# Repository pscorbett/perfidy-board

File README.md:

# perfidy-board
A truely diabolitcal perf board.

## Project Description
Generic perf board with a surprise mid-layer routing. I wouldn't wish this on my worst enemies!

## Manufacturing Note
If, for some godforesaken reason, you decide to produce this idiotic perf board, there are a few things you should be aware of:
1) I have never produced or tested it (Why would I??)
2) You need to select 4-layer manufacturing, which will be slightly more expensive than simple 2-layer boards. The board is set up with JLC PCB rules (but again, untested)
3) You will lose all of your friends

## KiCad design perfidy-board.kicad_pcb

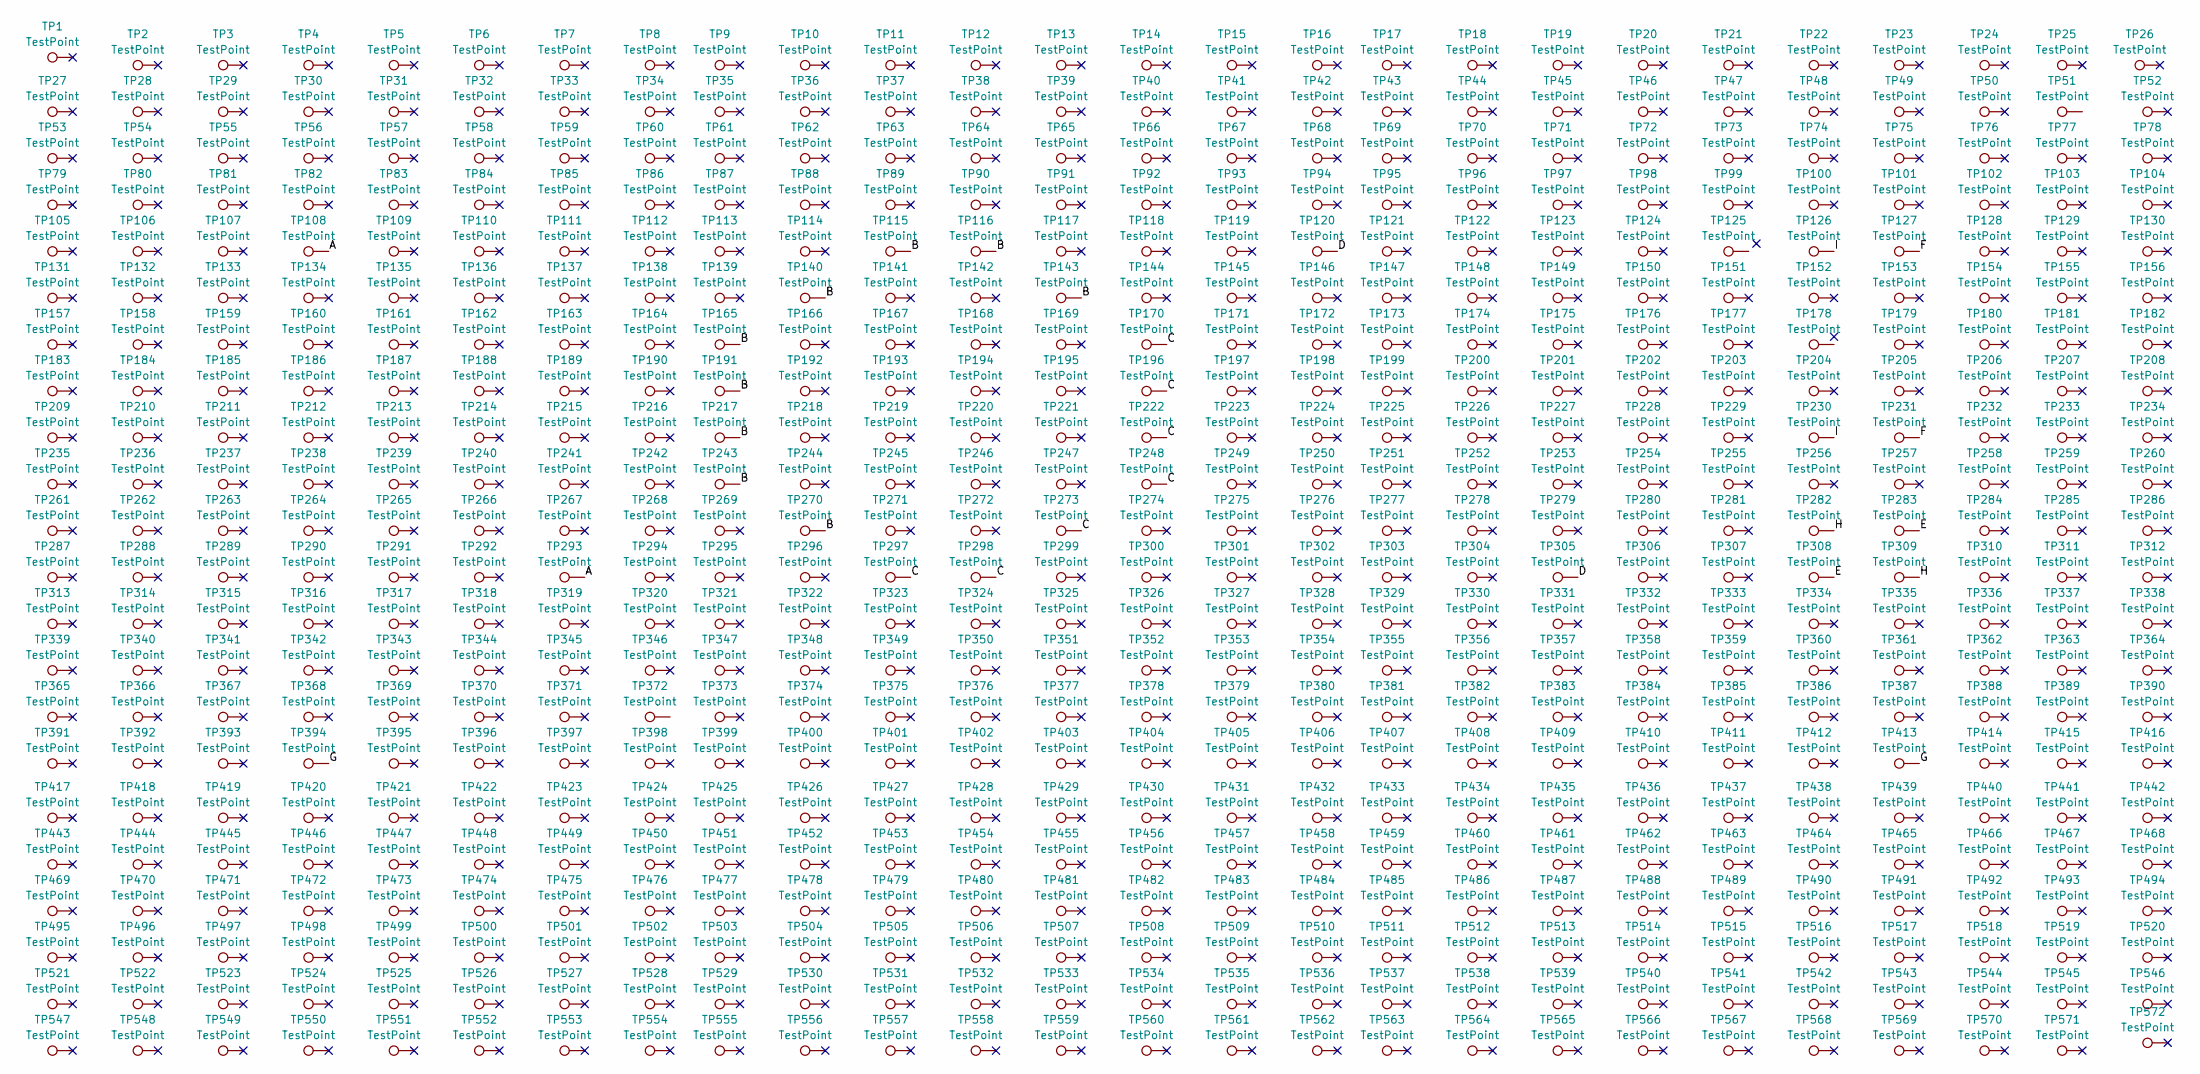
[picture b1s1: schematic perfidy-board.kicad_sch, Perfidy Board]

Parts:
TP1, TP26, TP547, TP572: TestPoint; Modified_MountingHole_3.2mm_M3_DIN965_Pad
TP2, TP3, TP4, TP5, TP6, TP7, TP8, TP9, TP10, TP11, TP12, TP13, TP14, TP15, TP16, TP17, TP18, TP19, TP20, TP21, TP22, TP23, TP24, TP25, TP27, TP28, TP29, TP30, TP31, TP32, TP33, TP34, TP35, TP36, TP37, TP38, TP39, TP40, TP41, TP42, TP43, TP44, TP45, TP46, TP47, TP48, TP49, TP50, TP51, TP52, TP53, TP54, TP55, TP56, TP57, TP58, TP59, TP60, TP61, TP62, TP63, TP64, TP65, TP66, TP67, TP68, TP69, TP70, TP71, TP72, TP73, TP74, TP75, TP76, TP77, TP78, TP79, TP80, TP81, TP82, TP83, TP84, TP85, TP86, TP87, TP88, TP89, TP90, TP91, TP92, TP93, TP94, TP95, TP96, TP97, TP98, TP99, TP100, TP101, TP102, TP103, TP104, TP105, TP106, TP107, TP108, TP109, TP110, TP111, TP112, TP113, TP114, TP115, TP116, TP117, TP118, TP119, TP120, TP121, TP122, TP123, TP124, TP125, TP126, TP127, TP128, TP129, TP130, TP131, TP132, TP133, TP134, TP135, TP136, TP137, TP138, TP139, TP140, TP141, TP142, TP143, TP144, TP145, TP146, TP147, TP148, TP149, TP150, TP151, TP152, TP153, TP154, TP155, TP156, TP157, TP158, TP159, TP160, TP161, TP162, TP163, TP164, TP165, TP166, TP167, TP168, TP169, TP170, TP171, TP172, TP173, TP174, TP175, TP176, TP177, TP178, TP179, TP180, TP181, TP182, TP183, TP184, TP185, TP186, TP187, TP188, TP189, TP190, TP191, TP192, TP193, TP194, TP195, TP196, TP197, TP198, TP199, TP200, TP201, TP202, TP203, TP204, TP205, TP206, TP207, TP208, TP209, TP210, TP211, TP212, TP213, TP214, TP215, TP216, TP217, TP218, TP219, TP220, TP221, TP222, TP223, TP224, TP225, TP226, TP227, TP228, TP229, TP230, TP231, TP232, TP233, TP234, TP235, TP236, TP237, TP238, TP239, TP240, TP241, TP242, TP243, TP244, TP245, TP246, TP247, TP248, TP249, TP250, TP251, TP252, TP253, TP254, TP255, TP256, TP257, TP258, TP259, TP260, TP261, TP262, TP263, TP264, TP265, TP266, TP267, TP268, TP269, TP270, TP271, TP272, TP273, TP274, TP275, TP276, TP277, TP278, TP279, TP280, TP281, TP282, TP283, TP284, TP285, TP286, TP287, TP288, TP289, TP290, TP291, TP292, TP293, TP294, TP295, TP296, TP297, TP298, TP299, TP300, TP301, TP302, TP303, TP304, TP305, TP306, TP307, TP308, TP309, TP310, TP311, TP312, TP313, TP314, TP315, TP316, TP317, TP318, TP319, TP320, TP321, TP322, TP323, TP324, TP325, TP326, TP327, TP328, TP329, TP330, TP331, TP332, TP333, TP334, TP335, TP336, TP337, TP338, TP339, TP340, TP341, TP342, TP343, TP344, TP345, TP346, TP347, TP348, TP349, TP350, TP351, TP352, TP353, TP354, TP355, TP356, TP357, TP358, TP359, TP360, TP361, TP362, TP363, TP364, TP365, TP366, TP367, TP368, TP369, TP370, TP371, TP372, TP373, TP374, TP375, TP376, TP377, TP378, TP379, TP380, TP381, TP382, TP383, TP384, TP385, TP386, TP387, TP388, TP389, TP390, TP391, TP392, TP393, TP394, TP395, TP396, TP397, TP398, TP399, TP400, TP401, TP402, TP403, TP404, TP405, TP406, TP407, TP408, TP409, TP410, TP411, TP412, TP413, TP414, TP415, TP416, TP417, TP418, TP419, TP420, TP421, TP422, TP423, TP424, TP425, TP426, TP427, TP428, TP429, TP430, TP431, TP432, TP433, TP434, TP435, TP436, TP437, TP438, TP439, TP440, TP441, TP442, TP443, TP444, TP445, TP446, TP447, TP448, TP449, TP450, TP451, TP452, TP453, TP454, TP455, TP456, TP457, TP458, TP459, TP460, TP461, TP462, TP463, TP464, TP465, TP466, TP467, TP468, TP469, TP470, TP471, TP472, TP473, TP474, TP475, TP476, TP477, TP478, TP479, TP480, TP481, TP482, TP483, TP484, TP485, TP486, TP487, TP488, TP489, TP490, TP491, TP492, TP493, TP494, TP495, TP496, TP497, TP498, TP499, TP500, TP501, TP502, TP503, TP504, TP505, TP506, TP507, TP508, TP509, TP510, TP511, TP512, TP513, TP514, TP515, TP516, TP517, TP518, TP519, TP520, TP521, TP522, TP523, TP524, TP525, TP526, TP527, TP528, TP529, TP530, TP531, TP532, TP533, TP534, TP535, TP536, TP537, TP538, TP539, TP540, TP541, TP542, TP543, TP544, TP545, TP546, TP548, TP549, TP550, TP551, TP552, TP553, TP554, TP555, TP556, TP557, TP558, TP559, TP560, TP561, TP562, TP563, TP564, TP565, TP566, TP567, TP568, TP569, TP570, TP571: TestPoint; Modified_TestPoint_THTPad_2.0x2.0mm_Drill1.0mm

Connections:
/A: TP108.1, TP293.1
/B: TP115.1, TP116.1, TP140.1, TP143.1, TP165.1, TP191.1, TP217.1, TP243.1, TP270.1
/C: TP170.1, TP196.1, TP222.1, TP248.1, TP273.1, TP297.1, TP298.1
/D: TP120.1, TP305.1
/E: TP283.1, TP308.1
/F: TP127.1, TP231.1
/G: TP394.1, TP413.1
/H: TP282.1, TP309.1
/I: TP126.1, TP230.1

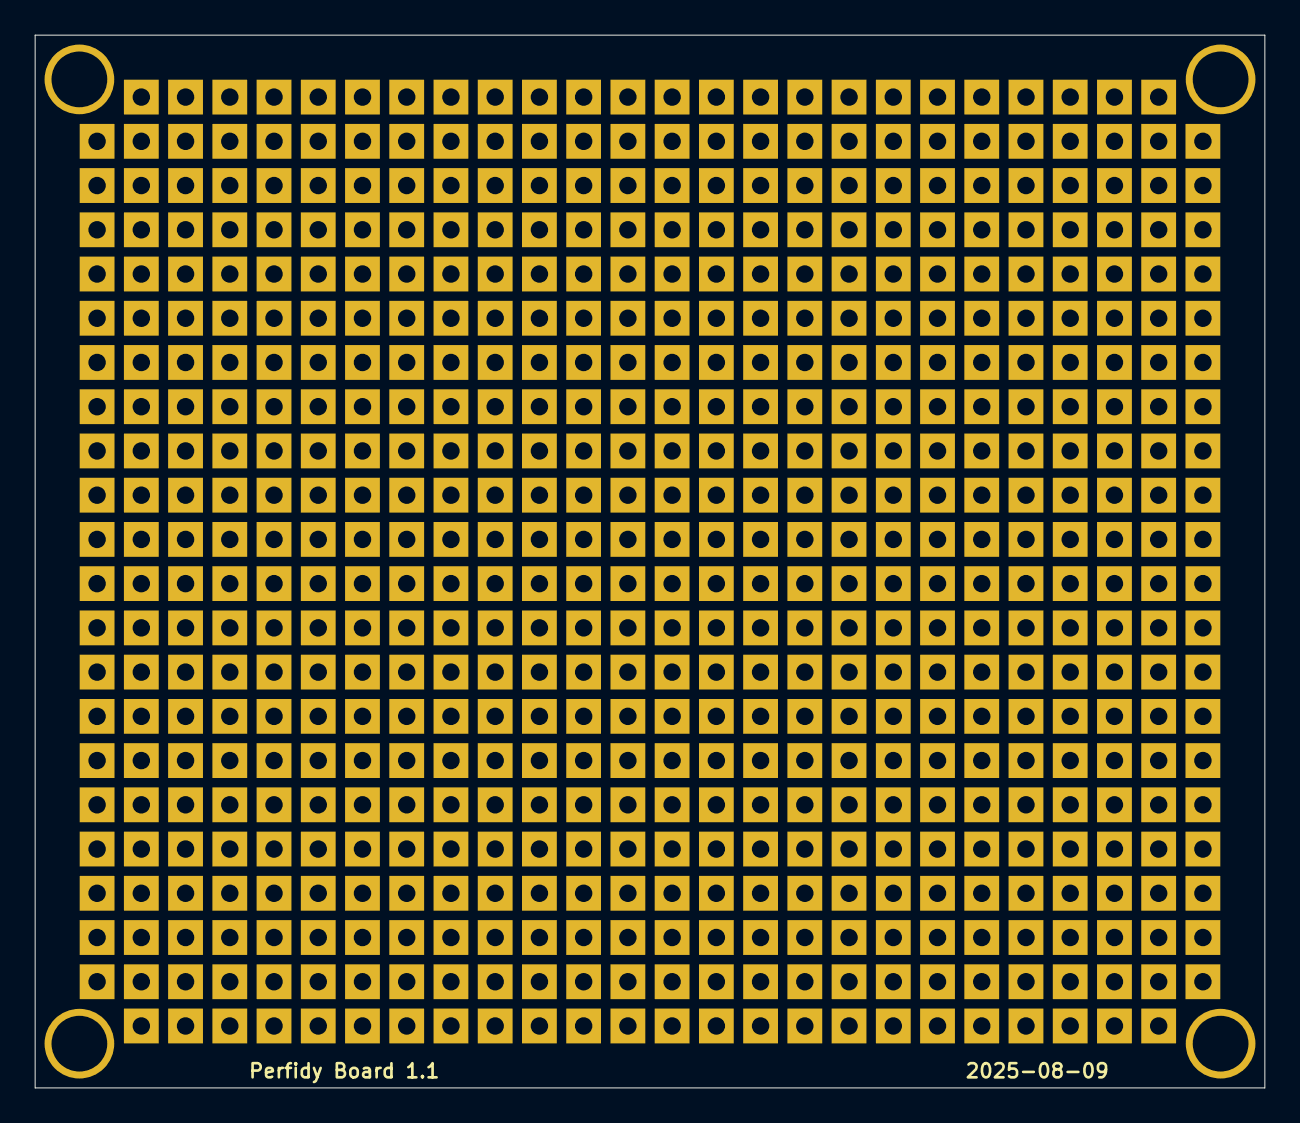
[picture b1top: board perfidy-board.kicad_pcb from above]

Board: 4 copper layers, 70.6 x 60.5 mm, 572 parts (0 on the bottom side), 9 nets.

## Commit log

2025-08-09 updating readme
    updating readme
2025-08-09 project update
2025-08-09 v1.1 changes mid layers to hidden text
